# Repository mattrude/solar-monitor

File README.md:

# Solar Monitor

A simple solution to prevent a solar powered LoRaWAN gateway from going into brownout when the batteries drop in voltages.

## The Backstory

I have a solar powered [Raspberry Pi](https://www.raspberrypi.org/) + [RAK2245](https://store.rakwireless.com/products/rak2245-pi-hat) + [RAK2013](https://store.rakwireless.com/products/rak2013-cellular-pi-hat) that has a problem where when it gets cold out, the batteries don't have the Amps to power the gateway when the sun comes up.  This puts the gateway into a brownout state where the cellular module disconnects and will not reconnect until the system is rebooted.

I have learned that a few minutes delay will resolve this issue, allow the batteries to charge and the system to boot correctly.  This project is an attempt to automate this task.

## Theory of Operation

When the voltage drops below about 3 volts, the `MCP102-300E/TO` will sit it's pin 2 `LOW`, once the voltages has stablized above 3 volts for more then 120 ms, pin 2 goes `HIGH`.

The `PIC16F15214-I/P` microcontroller reads the input from pin 2 on the `MCP102-300E/TO` (via pin 2 [INT] on the microcontroller) and set pin 0 `LOW`.  When microcontroller pin 0 is `LOW`, the `PN2222A` disables the power to the output pins of the board.

## Software

* [KiCad EDA](https://www.kicad.org/) - Version 6.0.2 - The Schematic & Board softare
* [MPLAB X IDE](https://www.microchip.com/en-us/tools-resources/develop/mplab-x-ide) - Version 6.0.0 - Software used to build the C code
  * [XC8](https://www.microchip.com/en-us/tools-resources/develop/mplab-xc-compilers) - Version 2.32 - The C compiler (A part of MPLAB X IDE)

## Hardware (BOM)

| **Identifier** | **Qty** | **Part #**      | **Description**    | **DigiKey**                                                                                                                      |
|:--------------:|:-------:|-----------------|--------------------|----------------------------------------------------------------------------------------------------------------------------------|
|       U1       | 1       | PIC16F15214-I/P | Microcontroller    | [150-PIC16F15214-I/P-ND](https://www.digikey.com/en/products/detail/microchip-technology/PIC16F15214-I-P/12807471)               |
|       Q1       | 1       | PN2222A         | Transistor         | [PN2222AFS-ND](https://www.digikey.com/en/products/detail/onsemi/PN2222ABU/6534)                                                 |
|       Q2       | 1       | MCP102-300E/TO  | Voltage Supervisor | [MCP102-300E/TO-ND](https://www.digikey.com/en/products/detail/microchip-technology/MCP102-300E-TO/716307)                       |
|       C1       | 1       | 10pF            | Ceramic Capacitor  | [K100K15C0GF53L2-ND](https://www.digikey.com/en/products/detail/vishay-beyschlag-draloric-bc-components/K100K15C0GF53L2/2820158) |
|       D1       | 1       | 1N914           | Diode              | [1N914FS-ND](https://www.digikey.com/en/products/detail/onsemi/1N914/978749)                                                     |
|       RV1      | 1       | PV36W103C01B00  | 10K Ohm Trimmer    | [490-2875-ND](https://www.digikey.com/en/products/detail/bourns-inc/PV36W103C01B00/666502)                                       |
|       SW1      | 1       | 1825910-6       | Push Button - 6mm  | [450-1650-ND](https://www.digikey.com/en/products/detail/te-connectivity-alcoswitch-switches/1825910-6/1632536)          |

## Schematic

## Board

**The Top of the Board**

**The Bottom of the Board**

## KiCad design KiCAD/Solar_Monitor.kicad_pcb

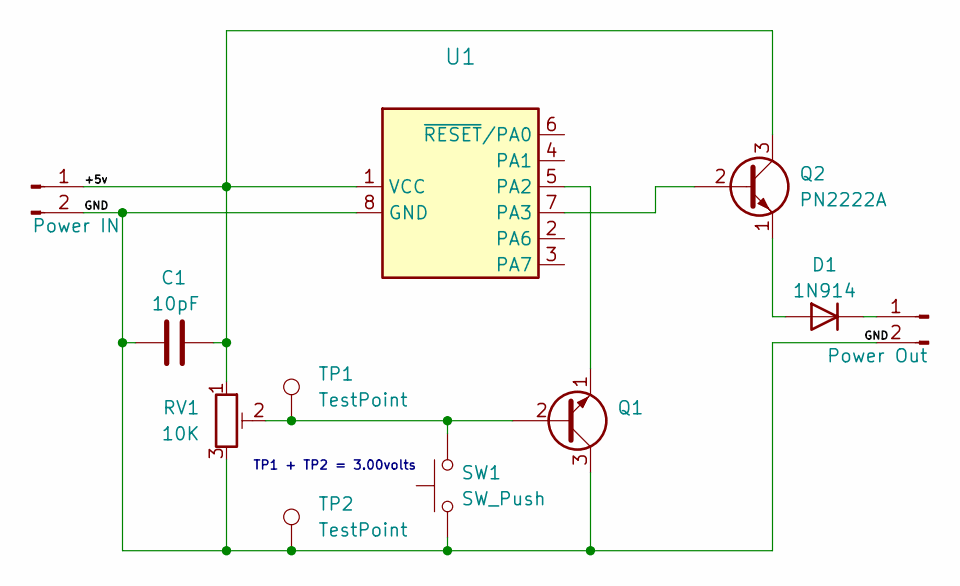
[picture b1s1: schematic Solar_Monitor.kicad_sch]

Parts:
C1: 10pF; C_Disc_D7.5mm_W2.5mm_P5.00mm
D1: 1N914; D_DO-35_SOD27_P7.62mm_Horizontal
J1: Power IN; PinHeader_1x02_P2.54mm_Vertical
J2: Power Out; PinHeader_1x02_P2.54mm_Vertical
Q1: TO-92
Q2: PN2222A; TO-92
RV1: 10K; Potentiometer_Bourns_3266Y_Vertical
SW1: SW_Push; SW_PUSH_6mm
TP1, TP2: TestPoint; TestPoint_Pad_D3.0mm
U1: SOIC-8_3.9x4.9mm_P1.27mm

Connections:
/+5v: C1.2, J1.1, Q2.3 (C), RV1.1, U1.1 (VCC)
/GND: C1.1, J1.2, J2.2, Q1.3, RV1.3, SW1.1, TP2.1, U1.8 (GND)
unnamed: D1.1 (K), J2.1
unnamed: D1.2 (A), Q2.1 (E)
unnamed: Q1.1, U1.5 (PA2)
unnamed: Q1.2, RV1.2, SW1.2, TP1.1
unnamed: Q2.2 (B), U1.7 (PA3)

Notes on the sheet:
TP1 + TP2 = 3.00volts

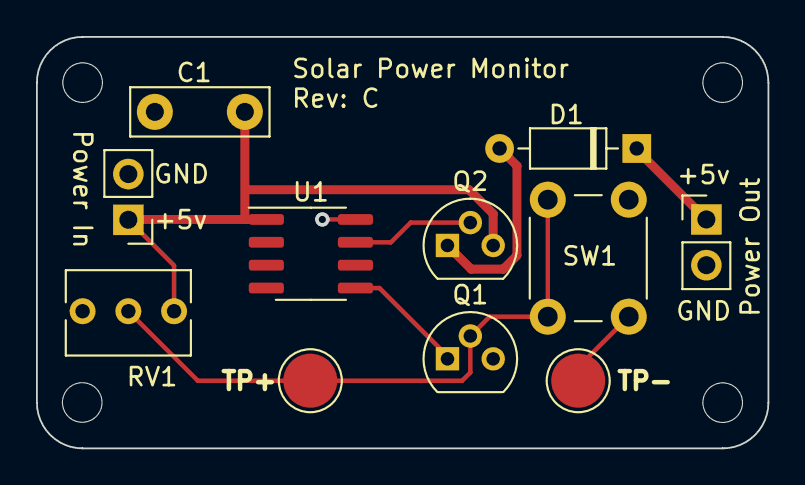
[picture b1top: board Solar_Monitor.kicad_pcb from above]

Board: 2 copper layers, 40.6 x 22.9 mm, 16 parts (1 on the bottom side), 7 nets.

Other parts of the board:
REF1, REF2, REF3, REF4: MountingHole_2.2mm_M2
REF5: OSHW-Logo2_7.3x6mm_SilkScreen

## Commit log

2022-02-16 Starting Out
2022-02-16 Add Images
2022-02-16 remove unneeded files
2022-02-16 Create LICENSE
2022-02-16 correct spelling
2022-02-16 Starting Rev: B
2022-02-16 Updating Images
2022-02-16 updates
    Update .gitignore
2022-02-16 Revert "updates"
    This reverts commit 69ab65feb4ee82550512227f35822cc277b56b4c.
2022-02-16 Correct c code
2022-02-16 try2
2022-02-16 Correct Folder Name
2022-02-16 correct name
2022-02-16 Change cntLastResets to 2
2022-02-16 Change to waiting 10 minutes after IRQ
2022-02-16 Wait for 5 minutes at boot
2022-02-16 minor commit change
2022-02-22 KiCAD: Added button
    Added button to reset the output for a set amount of time.
2022-02-22 A rewrite of the code
2022-02-22 Update images for RevB
2022-02-22 Create Garber_RevB.zip file
2022-02-22 Correct directory output
2022-02-22 minor update to pcb
2022-04-15 Rebuild Gerber files
2022-04-18 Remove cntHigh logic
2022-04-18 change max time to 30 minutes
2022-04-18 Correct watchdog
2022-04-19 Move interrupt to top of listing
2022-04-19 Move to tool chain v2.36 & xc8 v1.13.178
2022-04-19 Update .gitignore
    Remove:
    * MPLAB.X\nbproject\Makefile-default.mk
    * MPLAB.X\nbproject\Makefile-local-default.mk
    * MPLAB.X\nbproject\private\configurations.xml
2022-04-19 Update .gitignore
    %s/\///g
2022-04-19 Moving on
2022-04-19 Switch to an ATTiny402
2022-04-19 Remove PIC Code
2022-04-19 Move to Atmel Studio

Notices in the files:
KiCAD/Solar_Monitor.kicad_pcb:
©2022 Matt Rude
